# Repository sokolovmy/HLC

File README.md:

# HLC Home Light Controller 

v0.4 HW & FW

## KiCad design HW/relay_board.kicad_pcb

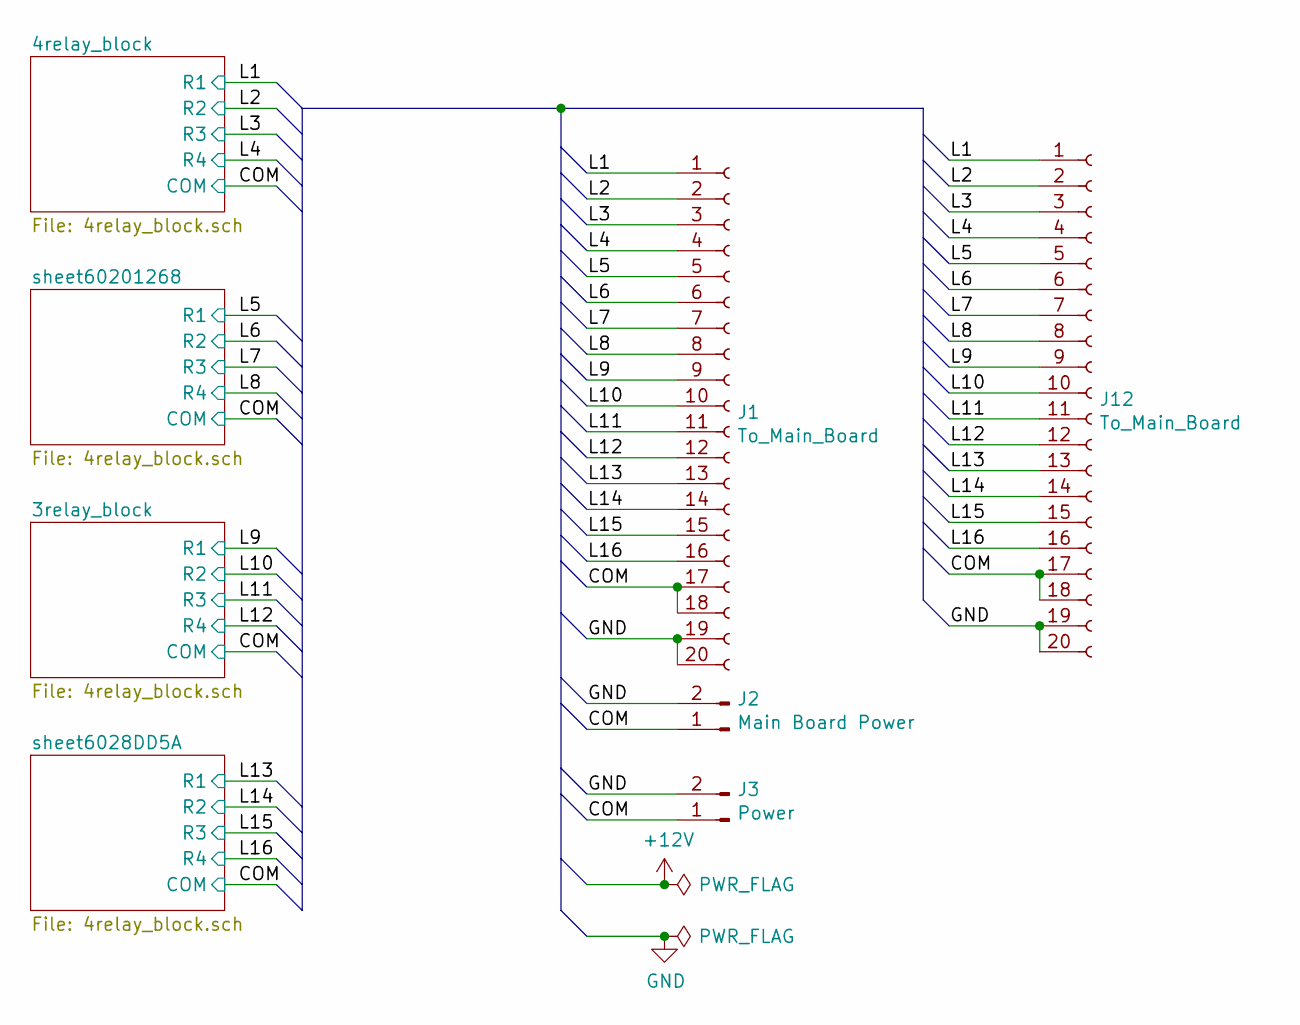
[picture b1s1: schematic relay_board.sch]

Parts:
J1: To_Main_Board; IDC-Header_2x10_P2.54mm_Vertical
J2: Main Board Power; SolderWire-0.5sqmm_1x02_P4.6mm_D0.9mm_OD2.1mm
J3: Power; PhoenixContact_MC_1,5_2-G-5.08_1x02_P5.08mm_Horizontal
J12: To_Main_Board; IDC-Header_2x10_P2.54mm_Horizontal

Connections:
/COM: J1.17, J1.18, J2.1, J3.1, J12.17, J12.18; also elsewhere on the board
/L1: J1.1, J12.1; also elsewhere on the board
/L2: J1.2, J12.2; also elsewhere on the board
/L3: J1.3, J12.3; also elsewhere on the board
/L4: J1.4, J12.4; also elsewhere on the board
/L5: J1.5, J12.5; also elsewhere on the board
/L6: J1.6, J12.6; also elsewhere on the board
/L7: J1.7, J12.7; also elsewhere on the board
/L8: J1.8, J12.8; also elsewhere on the board
/L9: J1.9, J12.9; also elsewhere on the board
/L10: J1.10, J12.10; also elsewhere on the board
/L11: J1.11, J12.11; also elsewhere on the board
/L12: J1.12, J12.12; also elsewhere on the board
/L13: J1.13, J12.13; also elsewhere on the board
/L14: J1.14, J12.14; also elsewhere on the board
/L15: J1.15, J12.15; also elsewhere on the board
/L16: J1.16, J12.16; also elsewhere on the board
GND: J1.19, J1.20, J2.2, J3.2, J12.19, J12.20

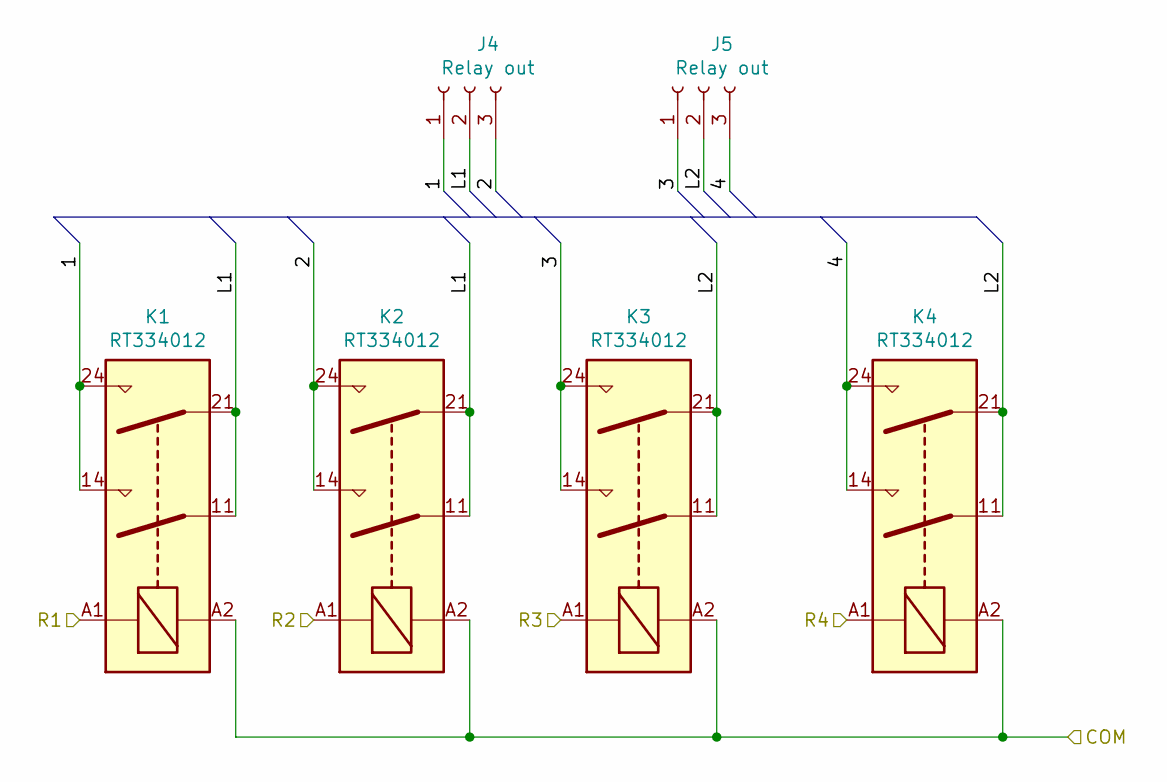
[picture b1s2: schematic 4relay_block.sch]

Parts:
J4, J5: Relay out; PhoenixContact_MC_1,5_3-G-5.08_1x03_P5.08mm_Horizontal
K1, K2, K3, K4: RT334012; Relay_DPST_Schrack-RT2-FormA_RM5mm

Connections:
/4relay_block/1: J4.1, K1.14, K1.24
/4relay_block/2: J4.3, K2.14, K2.24
/4relay_block/3: J5.1, K3.14, K3.24
/4relay_block/4: J5.3, K4.14, K4.24
/4relay_block/L1: J4.2, K1.11, K1.21, K2.11, K2.21
/4relay_block/L2: J5.2, K3.11, K3.21, K4.11, K4.21
/COM: K1.A2, K2.A2, K3.A2, K4.A2; also elsewhere on the board
/L1: K1.A1; also elsewhere on the board
/L2: K2.A1; also elsewhere on the board
/L3: K3.A1; also elsewhere on the board
/L4: K4.A1; also elsewhere on the board

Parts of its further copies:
J6, J7, J8, J9, J10, J11: Relay out; PhoenixContact_MC_1,5_3-G-5.08_1x03_P5.08mm_Horizontal
K5, K6, K7, K8, K9, K10, K11, K12, K13, K14, K15, K16: RT334012; Relay_DPST_Schrack-RT2-FormA_RM5mm

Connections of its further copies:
/3relay_block/1: J8.1, K9.14, K9.24
/3relay_block/2: J8.3, K10.14, K10.24
/3relay_block/3: J9.1, K11.14, K11.24
/3relay_block/4: J9.3, K12.14, K12.24
/3relay_block/L1: J8.2, K9.11, K9.21, K10.11, K10.21
/3relay_block/L2: J9.2, K11.11, K11.21, K12.11, K12.21
/COM: K5.A2, K6.A2, K7.A2, K8.A2, K9.A2, K10.A2, K11.A2, K12.A2, K13.A2, K14.A2, K15.A2, K16.A2; also elsewhere on the board
/L5: K5.A1; also elsewhere on the board
/L6: K6.A1; also elsewhere on the board
/L7: K7.A1; also elsewhere on the board
/L8: K8.A1; also elsewhere on the board
/L9: K9.A1; also elsewhere on the board
/L10: K10.A1; also elsewhere on the board
/L11: K11.A1; also elsewhere on the board
/L12: K12.A1; also elsewhere on the board
/L13: K13.A1; also elsewhere on the board
/L14: K14.A1; also elsewhere on the board
/L15: K15.A1; also elsewhere on the board
/L16: K16.A1; also elsewhere on the board
/sheet6028DD5A/1: J10.1, K13.14, K13.24
/sheet6028DD5A/2: J10.3, K14.14, K14.24
/sheet6028DD5A/3: J11.1, K15.14, K15.24
/sheet6028DD5A/4: J11.3, K16.14, K16.24
/sheet6028DD5A/L1: J10.2, K13.11, K13.21, K14.11, K14.21
/sheet6028DD5A/L2: J11.2, K15.11, K15.21, K16.11, K16.21
/sheet60201268/1: J6.1, K5.14, K5.24
/sheet60201268/2: J6.3, K6.14, K6.24
/sheet60201268/3: J7.1, K7.14, K7.24
/sheet60201268/4: J7.3, K8.14, K8.24
/sheet60201268/L1: J6.2, K5.11, K5.21, K6.11, K6.21
/sheet60201268/L2: J7.2, K7.11, K7.21, K8.11, K8.21

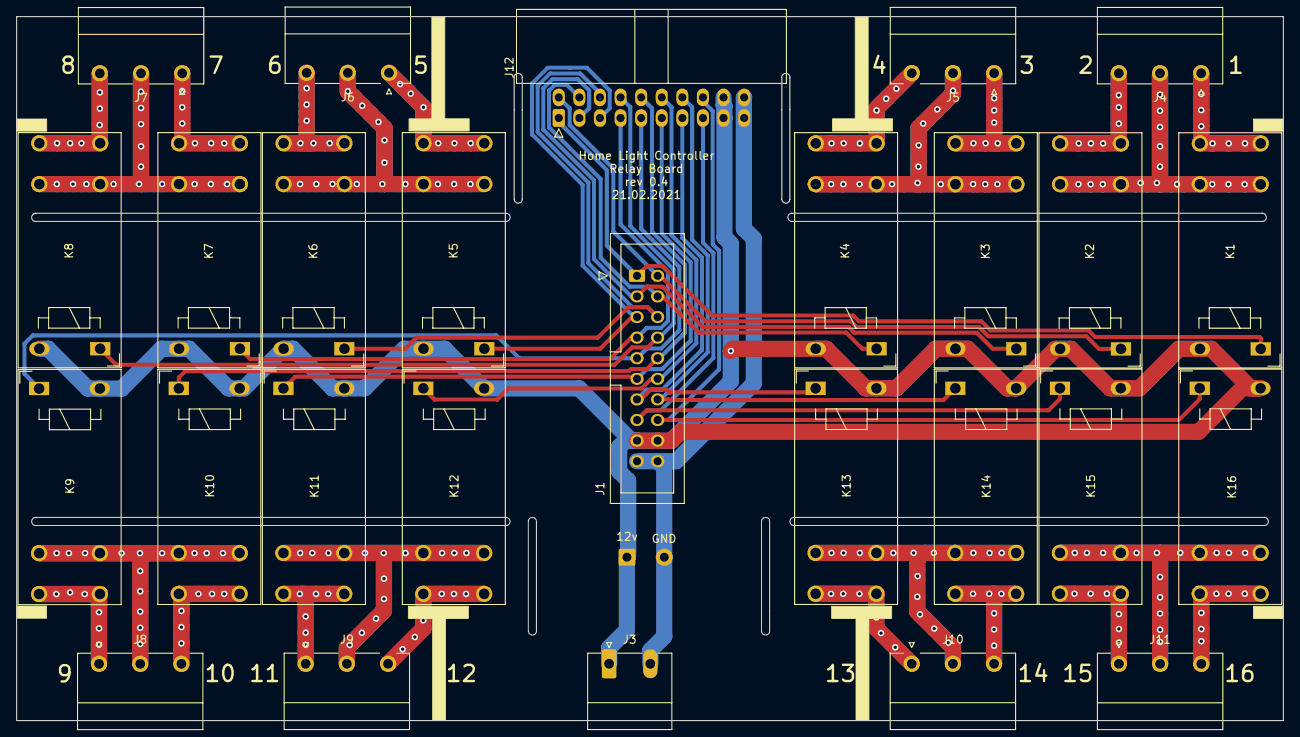
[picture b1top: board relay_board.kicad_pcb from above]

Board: 2 copper layers, 156.2 x 86.8 mm, 28 parts (0 on the bottom side), 42 nets.

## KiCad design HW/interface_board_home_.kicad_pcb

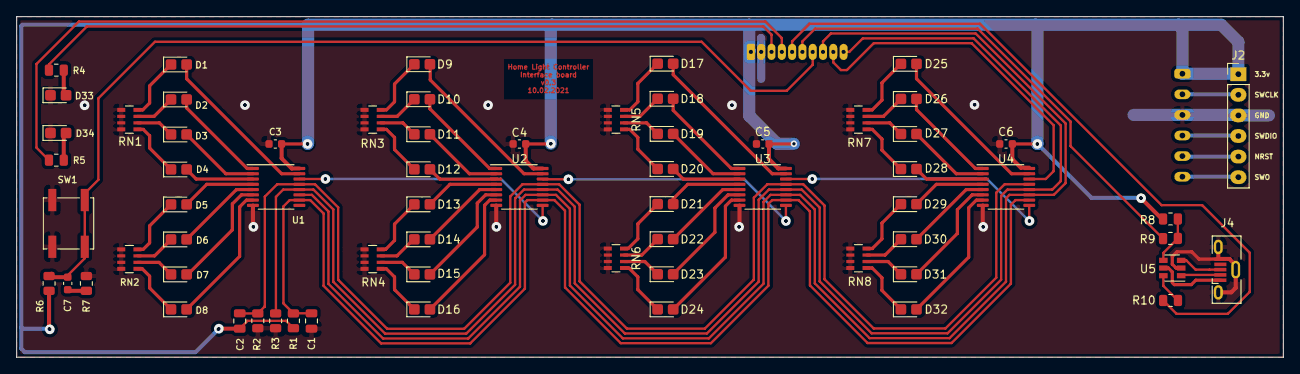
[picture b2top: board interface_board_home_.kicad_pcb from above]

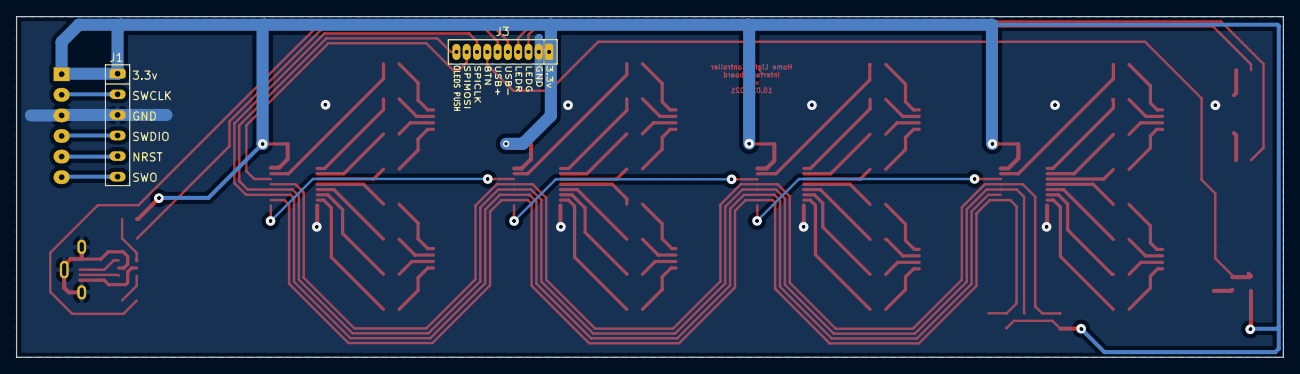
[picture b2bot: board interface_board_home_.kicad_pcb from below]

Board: 2 copper layers, 156.2 x 42.0 mm, 69 parts (2 on the bottom side), 91 nets.

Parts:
C1, C2: 1uF; C_0805_2012Metric
C3, C4, C5, C6: 0,1uF; C_0603_1608Metric
C7: 100nf; C_0603_1608Metric
D1, D2, D3, D4, D5, D6, D7, D8, D9, D10, D11, D12, D13, D14, D15, D16, D17, D18, D19, D20, D21, D22, D23, D24, D25, D26, D27, D28, D29, D30, D31, D32: LED; LED_0805_2012Metric_Castellated
D33: LEDG; LED_0805_2012Metric_Castellated
D34: LEDR; LED_0805_2012Metric_Castellated
J1: Program_M_Board; Program_Crossboard
J2: Program; PinHeader_1x06_P2.54mm_Vertical
J3: Crossboard
J4: USB_B_Micro; USB_Micro-B_Molex-105133-0001
R1, R2, R3, R6: 100k; R_0805_2012Metric
R4, R5: 10k; R_0805_2012Metric
R7: 100; R_0805_2012Metric
R8: 1.5k; R_0805_2012Metric
R9, R10: 22; R_0805_2012Metric
RN1, RN2, RN3, RN4, RN5, RN6, RN7, RN8: 10k; R_Array_Convex_4x0603
SW1: BTN; SW_SPST_EVPBF
U1, U2, U3, U4: 74HC595; TSSOP-16_4.4x5mm_P0.65mm
U5: USBLC6-2SC6; SOT-23-6

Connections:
/Output Leds/OEnable: C2.2, R2.2, U1.13, U2.13, U3.13, U4.13
/Output Leds/ONReg1: U1.14, U2.9
/Output Leds/ONReg2: U2.14, U3.9
/Output Leds/ONReg3: U3.14, U4.9
/Output Leds/Reset: C1.1, R1.1, U1.10, U2.10, U3.10, U4.10
BTN: C7.1, J3.7, R6.2, SW1.2
GND: C1.2, C3.2, C4.2, C5.2, C6.2, D33.1, D34.1, J1.3, J2.3, J3.2, J4.5, J4.6, R2.1, R3.1, R7.1, RN1.1, RN1.2, RN1.3, RN1.4, RN2.1, RN2.2, RN2.3, RN2.4, RN3.1, RN3.2, RN3.3, RN3.4, RN4.1, RN4.2, RN4.3, RN4.4, RN5.1, RN5.2, RN5.3, RN5.4, RN6.1, RN6.2, RN6.3, RN6.4, RN7.1, RN7.2, RN7.3, RN7.4, RN8.1, RN8.2, RN8.3, RN8.4, SW1.1, U1.8, U2.8, U3.8, U4.8, U5.2
LED_GREEN: J3.3, R4.1
LED_RED: J3.4, R5.1
unnamed: C7.2, R7.2
unnamed: D1.1, RN1.8
unnamed: D1.2, U1.15
unnamed: D2.1, RN1.7
unnamed: D2.2, U1.1
unnamed: D3.1, RN1.6
unnamed: D3.2, U1.2
unnamed: D4.1, RN1.5
unnamed: D4.2, U1.3
unnamed: D5.1, RN2.8
unnamed: D5.2, U1.4
unnamed: D6.1, RN2.7
unnamed: D6.2, U1.5
unnamed: D7.1, RN2.6
unnamed: D7.2, U1.6
unnamed: D8.1, RN2.5
unnamed: D8.2, U1.7
unnamed: D9.1, RN3.8
unnamed: D9.2, U2.15
unnamed: D10.1, RN3.7
unnamed: D10.2, U2.1
unnamed: D11.1, RN3.6
unnamed: D11.2, U2.2
unnamed: D12.1, RN3.5
unnamed: D12.2, U2.3
unnamed: D13.1, RN4.8
unnamed: D13.2, U2.4
unnamed: D14.1, RN4.7
unnamed: D14.2, U2.5
unnamed: D15.1, RN4.6
unnamed: D15.2, U2.6
unnamed: D16.1, RN4.5
unnamed: D16.2, U2.7
unnamed: D17.1, RN5.8
unnamed: D17.2, U3.15
unnamed: D18.1, RN5.7
unnamed: D18.2, U3.1
unnamed: D19.1, RN5.6
unnamed: D19.2, U3.2
unnamed: D20.1, RN5.5
unnamed: D20.2, U3.3
unnamed: D21.1, RN6.8
unnamed: D21.2, U3.4
unnamed: D22.1, RN6.7
unnamed: D22.2, U3.5
unnamed: D23.1, RN6.6
unnamed: D23.2, U3.6
unnamed: D24.1, RN6.5
unnamed: D24.2, U3.7
unnamed: D25.1, RN7.8
unnamed: D25.2, U4.15
unnamed: D26.1, RN7.7
unnamed: D26.2, U4.1
unnamed: D27.1, RN7.6
unnamed: D27.2, U4.2
unnamed: D28.1, RN7.5
unnamed: D28.2, U4.3
unnamed: D29.1, RN8.8
unnamed: D29.2, U4.4
unnamed: D30.1, RN8.7
unnamed: D30.2, U4.5
unnamed: D31.1, RN8.6
unnamed: D31.2, U4.6
unnamed: D32.1, RN8.5
unnamed: D32.2, U4.7
unnamed: D33.2, R4.2
unnamed: D34.2, R5.2
unnamed: J1.2, J2.2
unnamed: J1.4, J2.4
unnamed: J1.5, J2.5
unnamed: J1.6, J2.6
unnamed: J4.1, U5.5
unnamed: J4.2, U5.1
unnamed: J4.3, U5.3
unnamed: R8.1, R9.2, U5.4
unnamed: R10.2, U5.6
OLEDS_PUSH_DATA: J3.10, R3.2, U1.12, U2.12, U3.12, U4.12
SPICLK: J3.8, U1.11, U2.11, U3.11, U4.11
SPIMOSI: J3.9, U4.14
USB+: J3.6, R9.1
USB-: J3.5, R10.1
VCC: C2.1, C3.1, C4.1, C5.1, C6.1, J1.1, J2.1, J3.1, R1.2, R6.1, R8.2, U1.16, U2.16, U3.16, U4.16

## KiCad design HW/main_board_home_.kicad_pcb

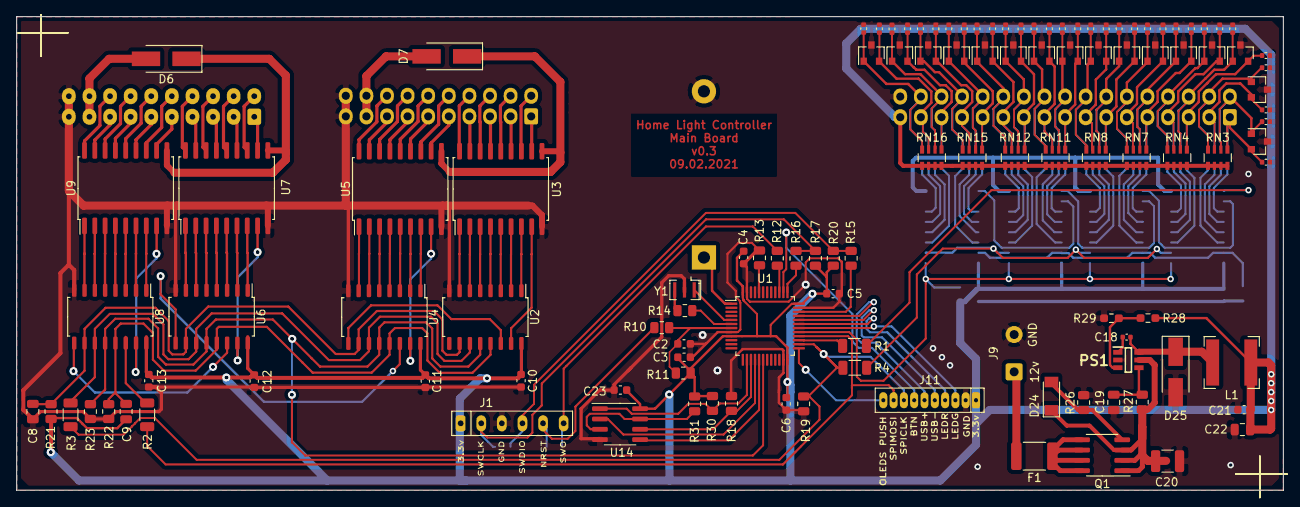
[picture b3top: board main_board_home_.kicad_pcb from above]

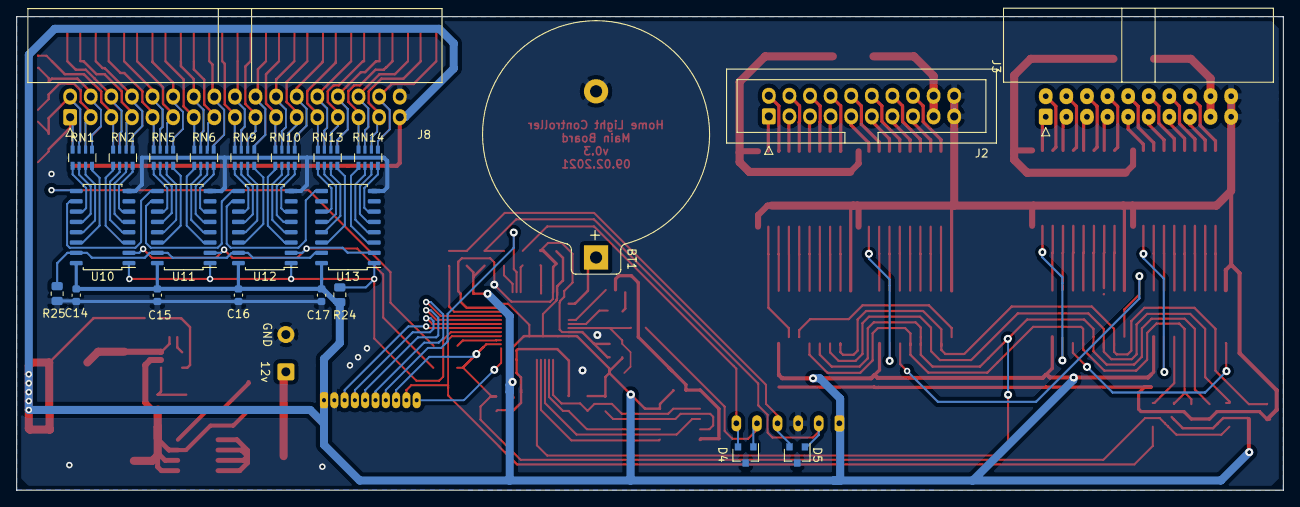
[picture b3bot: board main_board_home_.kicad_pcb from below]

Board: 2 copper layers, 156.2 x 58.4 mm, 143 parts (25 on the bottom side), 184 nets.

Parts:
BT1: 3v; BatteryHolder_Keystone_106_1x20mm
C2, C3, C4, C5, C6: 0.1uf; C_0603_1608Metric
C8, C9: 1uF; C_0805_2012Metric
C10, C11, C12, C13, C14, C15, C16, C17, C21: 0,1uF; C_0603_1608Metric
C18: 22nf; C_0402_1005Metric
C19: 10uF; C_0805_2012Metric
C20: 10uF/50v; C_1210_3225Metric
C22: 22uF; C_0805_2012Metric
C23: 0,1; C_0603_1608Metric
C24, C25, C26, C27, C28, C29, C30, C31, C32, C33, C34, C35, C36, C37, C38, C39, C40, C41, C42, C43, C44, C45, C46, C47, C48, C49, C50, C51, C52, C53, C54, C55: 0.1uf; C_0402_1005Metric
D4, D5, D8, D9, D10, D11, D12, D13, D14, D15, D16, D17, D18, D19, D20, D21, D22, D23: PESD3v3S2UT; SOT-23
D6, D7, D25: SS14; D_SMA_Handsoldering
D24: 10V/0.5W; D_MiniMELF
F1: 0.1A; Fuse_1812_4532Metric_Pad1.30x3.40mm_HandSolder
J1: Program; Program_Crossboard
J2: Conn_01x20_Male; IDC-Header_2x10_P2.54mm_Vertical
J3: Conn_01x20_Male; IDC-Header_2x10_P2.54mm_Horizontal
J8: Input Buttons; IDC-Header_2x17_P2.54mm_Horizontal
J9: Power_12V; SolderWire-0.5sqmm_1x02_P4.6mm_D0.9mm_OD2.1mm
J11: cross; Crossboard
L1: 10uH; L_Bourns-SRN6028
PS1: AP5100WG-7; SOT95P285X140-6N
Q1: FDS4435BZ; SOIC-8_3.9x4.9mm_P1.27mm
R1, R2, R3, R4: 0; R_1206_3216Metric
R10, R12, R15, R16: 22; R_0805_2012Metric
R11, R13, R17, R18, R19, R20, R21, R22, R23, R24, R25, R26, R27, R30, R31: 100k; R_0805_2012Metric
R14: 1k; R_0805_2012Metric
R28: 3,74k; R_0603_1608Metric_Pad0.98x0.95mm_HandSolder
R29: 1,21k; R_0603_1608Metric_Pad0.98x0.95mm_HandSolder
RN1, RN2, RN5, RN6, RN9, RN10, RN13, RN14: 1k; R_Array_Convex_4x0603
RN3, RN4, RN7, RN8, RN11, RN12, RN15, RN16: 10k; R_Array_Convex_4x0603
U1: STM32F103C8Tx; LQFP-48_7x7mm_P0.5mm
U2, U4, U6, U8: 74HC595; SOIC-16_4.55x10.3mm_P1.27mm
U3, U5, U7, U9: ULN2803A; SOIC-18W_7.5x11.6mm_P1.27mm
U10, U11, U12, U13: 74HC165; SOIC-16_4.55x10.3mm_P1.27mm
U14: M95256-WMN6P; SOIC-8_3.9x4.9mm_P1.27mm
Y1: 8mhz; Resonator_SMD_muRata_CSTxExxV-3Pin_3.0x1.1mm

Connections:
/BOOT0: R13.2, U1.44
/Inputs/Inputs8bit1/Cascade_Serial: U10.10, U11.9
/Inputs/Inputs8bit1/I1: C24.1, D8.2, J8.1, RN1.8, RN3.5
/Inputs/Inputs8bit1/I2: C25.1, D8.1, J8.2, RN1.7, RN3.6
/Inputs/Inputs8bit1/I3: C26.1, D9.2, J8.3, RN1.6, RN3.7
/Inputs/Inputs8bit1/I4: C27.1, D9.1, J8.4, RN1.5, RN3.8
/Inputs/Inputs8bit1/I5: C28.1, D10.2, J8.5, RN2.8, RN4.5
/Inputs/Inputs8bit1/I6: C29.1, D10.1, J8.6, RN2.7, RN4.6
/Inputs/Inputs8bit1/I7: C30.1, D11.2, J8.7, RN2.6, RN4.7
/Inputs/Inputs8bit1/I8: C31.1, D11.1, J8.8, RN2.5, RN4.8
/Inputs/Inputs8bit2/Cascade_Serial: U11.10, U12.9
/Inputs/Inputs8bit2/I1: C32.1, D12.2, J8.9, RN5.8, RN7.5
/Inputs/Inputs8bit2/I2: C33.1, D12.1, J8.10, RN5.7, RN7.6
/Inputs/Inputs8bit2/I3: C34.1, D13.2, J8.11, RN5.6, RN7.7
/Inputs/Inputs8bit2/I4: C35.1, D13.1, J8.12, RN5.5, RN7.8
/Inputs/Inputs8bit2/I5: C36.1, D14.2, J8.13, RN6.8, RN8.5
/Inputs/Inputs8bit2/I6: C37.1, D14.1, J8.14, RN6.7, RN8.6
/Inputs/Inputs8bit2/I7: C38.1, D15.2, J8.15, RN6.6, RN8.7
/Inputs/Inputs8bit2/I8: C39.1, D15.1, J8.16, RN6.5, RN8.8
/Inputs/Inputs8bit3/Cascade_Serial: U12.10, U13.9
/Inputs/Inputs8bit3/I1: C40.1, D16.2, J8.17, RN9.8, RN11.5
/Inputs/Inputs8bit3/I2: C41.1, D16.1, J8.18, RN9.7, RN11.6
/Inputs/Inputs8bit3/I3: C42.1, D17.2, J8.19, RN9.6, RN11.7
/Inputs/Inputs8bit3/I4: C43.1, D17.1, J8.20, RN9.5, RN11.8
/Inputs/Inputs8bit3/I5: C44.1, D18.2, J8.21, RN10.8, RN12.5
/Inputs/Inputs8bit3/I6: C45.1, D18.1, J8.22, RN10.7, RN12.6
/Inputs/Inputs8bit3/I7: C46.1, D19.2, J8.23, RN10.6, RN12.7
/Inputs/Inputs8bit3/I8: C47.1, D19.1, J8.24, RN10.5, RN12.8
/Inputs/Inputs8bit4/I1: C48.1, D20.2, J8.25, RN13.8, RN15.5
/Inputs/Inputs8bit4/I2: C49.1, D20.1, J8.26, RN13.7, RN15.6
/Inputs/Inputs8bit4/I3: C50.1, D21.2, J8.27, RN13.6, RN15.7
/Inputs/Inputs8bit4/I4: C51.1, D21.1, J8.28, RN13.5, RN15.8
/Inputs/Inputs8bit4/I5: C52.1, D22.2, J8.29, RN14.8, RN16.5
/Inputs/Inputs8bit4/I6: C53.1, D22.1, J8.30, RN14.7, RN16.6
/Inputs/Inputs8bit4/I7: C54.1, D23.2, J8.31, RN14.6, RN16.7
/Inputs/Inputs8bit4/I8: C55.1, D23.1, J8.32, RN14.5, RN16.8
/Inputs/in_CLK_Inhb: R25.1, U10.15, U11.15, U12.15, U13.15
/Outputs/OEnable: C9.2, R22.2, U2.13, U4.13, U6.13, U8.13
/Outputs/ONReg1: U2.14, U4.9
/Outputs/ONReg2: U4.14, U6.9
/Outputs/ONReg3: U6.14, U8.9
/Outputs/Outputs8bit/lo1: U2.15, U3.8
/Outputs/Outputs8bit/lo2: U2.1, U3.7
/Outputs/Outputs8bit/lo3: U2.2, U3.6
/Outputs/Outputs8bit/lo4: U2.3, U3.5
/Outputs/Outputs8bit/lo5: U2.4, U3.4
/Outputs/Outputs8bit/lo6: U2.5, U3.3
/Outputs/Outputs8bit/lo7: U2.6, U3.2
/Outputs/Outputs8bit/lo8: U2.7, U3.1
/Outputs/Reset: C8.1, R21.1, U2.10, U4.10, U6.10, U8.10
/Outputs/oa1: J2.1, U3.11
/Outputs/oa2: J2.2, U3.12
/Outputs/oa3: J2.3, U3.13
/Outputs/oa4: J2.4, U3.14
/Outputs/oa5: J2.5, U3.15
/Outputs/oa6: J2.6, U3.16
/Outputs/oa7: J2.7, U3.17
/Outputs/oa8: J2.8, U3.18
/Outputs/oa9: J2.9, U5.11
/Outputs/oa10: J2.10, U5.12
/Outputs/oa11: J2.11, U5.13
/Outputs/oa12: J2.12, U5.14
/Outputs/oa13: J2.13, U5.15
/Outputs/oa14: J2.14, U5.16
/Outputs/oa15: J2.15, U5.17
/Outputs/oa16: J2.16, U5.18
/Outputs/oa17: J3.1, U7.11
/Outputs/oa18: J3.2, U7.12
/Outputs/oa19: J3.3, U7.13
/Outputs/oa20: J3.4, U7.14
/Outputs/oa21: J3.5, U7.15
/Outputs/oa22: J3.6, U7.16
/Outputs/oa23: J3.7, U7.17
/Outputs/oa24: J3.8, U7.18
/Outputs/oa25: J3.9, U9.11
/Outputs/oa26: J3.10, U9.12
/Outputs/oa27: J3.11, U9.13
/Outputs/oa28: J3.12, U9.14
/Outputs/oa29: J3.13, U9.15
/Outputs/oa30: J3.14, U9.16
/Outputs/oa31: J3.15, U9.17
/Outputs/oa32: J3.16, U9.18
/Outputs/oaCOM: D7.1, U3.10, U5.10
/Outputs/oaCOM2: D6.1, U7.10, U9.10
/Outputs/sheet603D1D0F/lo1: U6.15, U7.8
/Outputs/sheet603D1D0F/lo2: U6.1, U7.7
/Outputs/sheet603D1D0F/lo3: U6.2, U7.6
/Outputs/sheet603D1D0F/lo4: U6.3, U7.5
/Outputs/sheet603D1D0F/lo5: U6.4, U7.4
/Outputs/sheet603D1D0F/lo6: U6.5, U7.3
/Outputs/sheet603D1D0F/lo7: U6.6, U7.2
/Outputs/sheet603D1D0F/lo8: U6.7, U7.1
/Outputs/sheet6038A325/lo1: U4.15, U5.8
/Outputs/sheet6038A325/lo2: U4.1, U5.7
/Outputs/sheet6038A325/lo3: U4.2, U5.6
/Outputs/sheet6038A325/lo4: U4.3, U5.5
/Outputs/sheet6038A325/lo5: U4.4, U5.4
/Outputs/sheet6038A325/lo6: U4.5, U5.3
/Outputs/sheet6038A325/lo7: U4.6, U5.2
/Outputs/sheet6038A325/lo8: U4.7, U5.1
/Outputs/sheet60400210/lo1: U8.15, U9.8
/Outputs/sheet60400210/lo2: U8.1, U9.7
/Outputs/sheet60400210/lo3: U8.2, U9.6
/Outputs/sheet60400210/lo4: U8.3, U9.5
/Outputs/sheet60400210/lo5: U8.4, U9.4
/Outputs/sheet60400210/lo6: U8.5, U9.3
/Outputs/sheet60400210/lo7: U8.6, U9.2
/Outputs/sheet60400210/lo8: U8.7, U9.1
BTN: J11.7, U1.38
EEPROM_SELECT: R30.2, U1.14, U14.1
GND: BT1.2, C2.2, C3.2, C4.2, C5.2, C6.2, C8.2, C10.2, C11.2, C12.2, C13.2, C14.2, C15.2, C16.2, C17.2, C19.2, C20.1, C21.2, C22.2, C23.1, C24.2, C25.2, C26.2, C27.2, C28.2, C29.2, C30.2, C31.2, C32.2, C33.2, C34.2, C35.2, C36.2, C37.2, C38.2, C39.2, C40.2, C41.2, C42.2, C43.2, C44.2, C45.2, C46.2, C47.2, C48.2, C49.2, C50.2, C51.2, C52.2, C53.2, C54.2, C55.2, D4.3, D5.3, D8.3, D9.3, D10.3, D11.3, D12.3, D13.3, D14.3, D15.3, D16.3, D17.3, D18.3, D19.3, D20.3, D21.3, D22.3, D23.3, D25.2, J1.3, J2.19, J2.20, J3.19, J3.20, J8.34, J9.2, J11.2, PS1.2, R13.1, R18.2, R19.2, R22.1, R23.1, R25.2, R26.2, R29.2, U1.8, U1.23, U1.35, U1.47, U2.8, U3.9, U4.8, U5.9, U6.8, U7.9, U8.8, U9.9, U10.8, U11.8, U12.8, U13.8, U14.4, Y1.2
IN_CLK: R4.1, U10.2, U11.2, U12.2, U13.2
IN_Load: R24.1, U1.29, U10.1, U11.1, U12.1, U13.1
IN_Serial: R1.1, U10.9
LED_GREEN: J11.3, U1.30
LED_RED: J11.4, U1.31
NRST: D4.1, J1.5, R10.1
unnamed: BT1.1, U1.1
unnamed: C2.1, R10.2, R11.1, U1.7
unnamed: C18.1, D25.1, L1.1, PS1.6
unnamed: C18.2, PS1.1
unnamed: C19.1, PS1.4, R27.2
unnamed: C20.2, D24.1, PS1.5, Q1.1, Q1.2, Q1.3, R27.1
unnamed: D6.2, J3.17, J3.18
unnamed: D7.2, J2.17, J2.18
unnamed: D24.2, Q1.4, R26.1
unnamed: F1.1, Q1.5, Q1.6, Q1.7, Q1.8
unnamed: F1.2, J9.1
unnamed: PS1.3, R28.2, R29.1
unnamed: R12.1, U1.39
unnamed: R14.1, Y1.3
unnamed: R14.2, U1.6
unnamed: R15.1, U1.34
unnamed: R16.1, U1.37
unnamed: R31.2, U14.3, U14.7
unnamed: RN1.1, U10.11
unnamed: RN1.2, U10.12
unnamed: RN1.3, U10.13
unnamed: RN1.4, U10.14
unnamed: RN2.1, U10.3
unnamed: RN2.2, U10.4
unnamed: RN2.3, U10.5
unnamed: RN2.4, U10.6
unnamed: RN5.1, U11.11
unnamed: RN5.2, U11.12
unnamed: RN5.3, U11.13
unnamed: RN5.4, U11.14
unnamed: RN6.1, U11.3
unnamed: RN6.2, U11.4
unnamed: RN6.3, U11.5
unnamed: RN6.4, U11.6
unnamed: RN9.1, U12.11
unnamed: RN9.2, U12.12
unnamed: RN9.3, U12.13
unnamed: RN9.4, U12.14
unnamed: RN10.1, U12.3
unnamed: RN10.2, U12.4
unnamed: RN10.3, U12.5
unnamed: RN10.4, U12.6
unnamed: RN13.1, U13.11
unnamed: RN13.2, U13.12
unnamed: RN13.3, U13.13
unnamed: RN13.4, U13.14
unnamed: RN14.1, U13.3
unnamed: RN14.2, U13.4
unnamed: RN14.3, U13.5
unnamed: RN14.4, U13.6
unnamed: U1.5, Y1.1
OUT_CLK: R3.1, U2.11, U4.11, U6.11, U8.11
OUT_LED_ENABLE: J11.10, U1.25
OUT_Push_Data: R23.2, U1.18, U2.12, U4.12, U6.12, U8.12
OUT_Serial: R2.1, U8.14
SPI1_CLK: R18.1, U1.15, U14.6
SPI1_MISO: U1.16, U14.2
SPI1_MOSI: U1.17, U14.5
SPI2_CLK: J11.8, R3.2, R4.2, R19.1, U1.26
SPI2_MISO: R1.2, U1.27
SPI2_MOSI: J11.9, R2.2, U1.28
SWCLK: D5.1, J1.2, R16.2, R17.2
SWDIO: D5.2, J1.4, R15.2, R20.2
SWO: D4.2, J1.6, R12.2
USB+: J11.6, U1.33
USB-: J11.5, U1.32
VCC: C3.1, C4.1, C5.1, C6.1, C9.1, C10.1, C11.1, C12.1, C13.1, C14.1, C15.1, C16.1, C17.1, C21.1, C22.1, C23.2, J1.1, J8.33, J11.1, L1.2, R11.2, R17.1, R20.1, R21.2, R24.2, R28.1, R30.1, R31.1, RN3.1, RN3.2, RN3.3, RN3.4, RN4.1, RN4.2, RN4.3, RN4.4, RN7.1, RN7.2, RN7.3, RN7.4, RN8.1, RN8.2, RN8.3, RN8.4, RN11.1, RN11.2, RN11.3, RN11.4, RN12.1, RN12.2, RN12.3, RN12.4, RN15.1, RN15.2, RN15.3, RN15.4, RN16.1, RN16.2, RN16.3, RN16.4, U1.9, U1.24, U1.36, U1.48, U2.16, U4.16, U6.16, U8.16, U10.16, U11.16, U12.16, U13.16, U14.8

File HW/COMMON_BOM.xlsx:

Reference | Quantity | Value | Footprint | LCSC Part | P/N | Arrow Part Number | %
BT1 | 1 | 3v | Battery:BatteryHolder_Keystone_106_1x20mm
C1 | 1 | 100pf | Capacitor_SMD:C_0402_1005Metric | C696853
C10 C11 C12 C13 C14 C15 C16 C17 C21 | 9 | 0,1uF | Capacitor_SMD:C_0402_1005Metric | C83056
C18 | 1 | 22nf | Capacitor_SMD:C_0402_1005Metric | C466237
C19 | 1 | 10uF | Capacitor_SMD:C_0805_2012Metric | C337995
C2 C3 C4 C5 C6 C23 C24 C25 C26 C27 C28 C29 C30 C31 C32 C33 C34 C35 C36 C37 C38 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 | 38 | 100nf | Capacitor_SMD:C_0402_1005Metric | C83056
C20 | 1 | 22uF/25v | Capacitor_SMD:C_0805_2012Metric_Pad1.18x1.45mm_HandSolder | C45783
C22 | 1 | 22uF | Capacitor_SMD:C_0805_2012Metric | C45783
C8 C9 | 2 | 1uF | Capacitor_SMD:C_0603_1608Metric | C1592
D24 | 1 | 10V/0.5W | Diode_SMD:D_MiniMELF | C707201
D4 D5 D8 D9 D10 D11 D12 D13 D14 D15 D16 D17 D18 D19 D20 D21 D22 D23 | 18 | PESD3v3S2UT | Package_TO_SOT_SMD:SOT-23 | C84276
D6 D7 D25 | 3 | SS14 | Diode_SMD:D_SMA_Handsoldering | C509048
F1 | 1 | 0.4A | Fuse:Fuse_1812_4532Metric_Pad1.30x3.40mm_HandSolder | C369179
J1 | 1 | Program | holse:Program_Crossboard
J11 | 1 | cross | holse:Crossboard
J2 | 1 | Conn_01x20_Male | holse:IDC-Header_2x10_P2.54mm_Vertical
J3 | 1 | Conn_01x20_Male | holse:IDC-Header_2x10_P2.54mm_Horizontal
J8 | 1 | Input Buttons | holse:IDC-Header_2x17_P2.54mm_Horizontal
J9 | 1 | Power_12V | holse:SolderWire-0.5sqmm_1x02_P4.6mm_D0.9mm_OD2.1mm
L1 | 1 | 10uH | Inductor_SMD:L_Bourns-SRN6028 | C326329
PS1 | 1 | AP5100WG-7 | holse:SOT95P285X140-6N | C114647 |  | AP5100WG-7
Q1 | 1 | FDS4435BZ | Package_SO:SOIC-8_3.9x4.9mm_P1.27mm | C23931
R10 R12 R15 R16 | 4 | 22 | Resistor_SMD:R_0603_1608Metric | C96423
R11 R13 R17 R18 R19 R20 R21 R22 R23 R24 R25 R26 R27 R30 R31 | 15 | 100k | Resistor_SMD:R_0603_1608Metric | C177329
R14 | 1 | 1k | Resistor_SMD:R_0603_1608Metric | C112433
R28 | 1 | 49.9k | Resistor_SMD:R_0603_1608Metric | C705862 |  |  | 0.1
R29 | 1 | 16.2k | Resistor_SMD:R_0603_1608Metric | C667056 |  |  | 0.1
RN1 RN2 RN5 RN6 RN9 RN10 RN13 RN14 | 8 | 1k | holse:R_Array_Convex_4x0603 | C153136
RN3 RN4 RN7 RN8 RN11 RN12 RN15 RN16 | 8 | 10k | holse:R_Array_Convex_4x0603 | C164037
U1 | 1 | STM32F103CBTx | Package_QFP:LQFP-48_7x7mm_P0.5mm | C8304
U10 U11 U12 U13 | 4 | 74HC165 | Package_SO:SOIC-16_4.55x10.3mm_P1.27mm | C7334
U14 | 1 | M95256-WMN6P | Package_SO:SOIC-8_3.9x4.9mm_P1.27mm | C222231
U2 U4 U6 U8 | 4 | 74HC595 | Package_SO:SOIC-16_4.55x10.3mm_P1.27mm | C5947
U3 U5 U7 U9 | 4 | ULN2803A | Package_SO:SOIC-18W_7.5x11.6mm_P1.27mm | C9683
Y1 | 1 | 8mhz | Crystal:Resonator_SMD_muRata_CSTxExxV-3Pin_3.0x1.1mm | C22549 | CSTCE8M00G52-R0 MuraTA

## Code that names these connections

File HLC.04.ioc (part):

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Mcu.Name=STM32F103C(8-B)Tx
Mcu.Package=LQFP48
Mcu.UserName=STM32F103CBTx
PA10.GPIOParameters=GPIO_Label
PA10.GPIO_Label=PIN_LED_RED
PA10.Signal=GPIO_Output
PA11.Mode=Device
PA11.Signal=USB_DM
PA12.Mode=Device
PA12.Signal=USB_DP
PA13.Mode=Trace_Asynchronous_SW
PA13.Signal=SYS_JTMS-SWDIO
PA14.Mode=Trace_Asynchronous_SW
PA14.Signal=SYS_JTCK-SWCLK
PA4.GPIOParameters=GPIO_Label
PA4.GPIO_Label=PIN_EEPROM_SELECT
PA4.Signal=GPIO_Output
PA5.Mode=Full_Duplex_Master
PA5.Signal=SPI1_SCK
PA6.Mode=Full_Duplex_Master
PA6.Signal=SPI1_MISO
PA7.Mode=Full_Duplex_Master
PA7.Signal=SPI1_MOSI
PA8.GPIOParameters=GPIO_Label
PA8.GPIO_Label=PIN_IN_LOAD
PA8.Signal=GPIO_Output
PA9.GPIOParameters=GPIO_Label
PA9.GPIO_Label=PIN_LED_GREEN
PA9.Signal=GPIO_Output
PB0.GPIOParameters=GPIO_Label
PB0.GPIO_Label=PIN_OUT_PUSH_DATA
PB0.Signal=GPIO_Output
PB11.GPIOParameters=GPIO_Label
PB11.GPIO_Label=PIN_BTN
PB11.Signal=GPIO_Input
PB12.GPIOParameters=GPIO_Label
PB12.GPIO_Label=PIN_OUT_LED_PUSH_DATA
PB12.Signal=GPIO_Output
PB13.Mode=Full_Duplex_Master
PB13.Signal=SPI2_SCK
PB14.Mode=Full_Duplex_Master
PB14.Signal=SPI2_MISO
PB15.Mode=Full_Duplex_Master
PB15.Signal=SPI2_MOSI
PB3.Mode=Trace_Asynchronous_SW
PB3.Signal=SYS_JTDO-TRACESWO
PD0-OSC_IN.Mode=HSE-External-Oscillator
PD0-OSC_IN.Signal=RCC_OSC_IN
PD1-OSC_OUT.Mode=HSE-External-Oscillator
PD1-OSC_OUT.Signal=RCC_OSC_OUT
RCC.SYSCLKFreq_VALUE=48000000
RCC.SYSCLKSource=RCC_SYSCLKSOURCE_PLLCLK
board=custom
